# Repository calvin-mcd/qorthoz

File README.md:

# qorthoz

qorthoz is an ortholinear 10.25u qaz compatible pcb with usb c and jst ports for case compatibility, rgb breakout strip and 6 additional pins for switch or rotary extensions.

## Layout

## Pictures

## Firmware

Firmware is written for vial and the source code is provided for edits.

## RGB Strip

Please note that the PCB is using a STM32 MCU which runs on 3v3 logic. Using a 5V rgb strip can sometimes interfere with the 3v3 Data Signal from the MCU. If you use a 5V rgb strip solder Data IN and GND to the beginning of the strip but *DO NOT* solder power to the beginning but anywhere else on the strip. This should be enough to avoid 5V Power interference with the 3v3 Data IN.

## Disclaimer

This PCB has been fully tested and is confirmed to work. However, no-one involved in this project is responsible for any usage issues that may arise. Order at your own risk. Feel free to edit, modify and otherwise utilise these files.

## License

This project is released under the GPL v3 License. Please refer to the LICENCE file.

## Credits

This pcb has been made on request kriscovery. Do check out their beautiful qaz and qez compatible cases! https://www.printables.com/@kriscovery

The silkscreen logo has been taken from the german 40s keyboard discord ClackTales!

As always big thanks to the many people who helped me and inspired this board!

Any questions, contact Calvin0563 on Discord.

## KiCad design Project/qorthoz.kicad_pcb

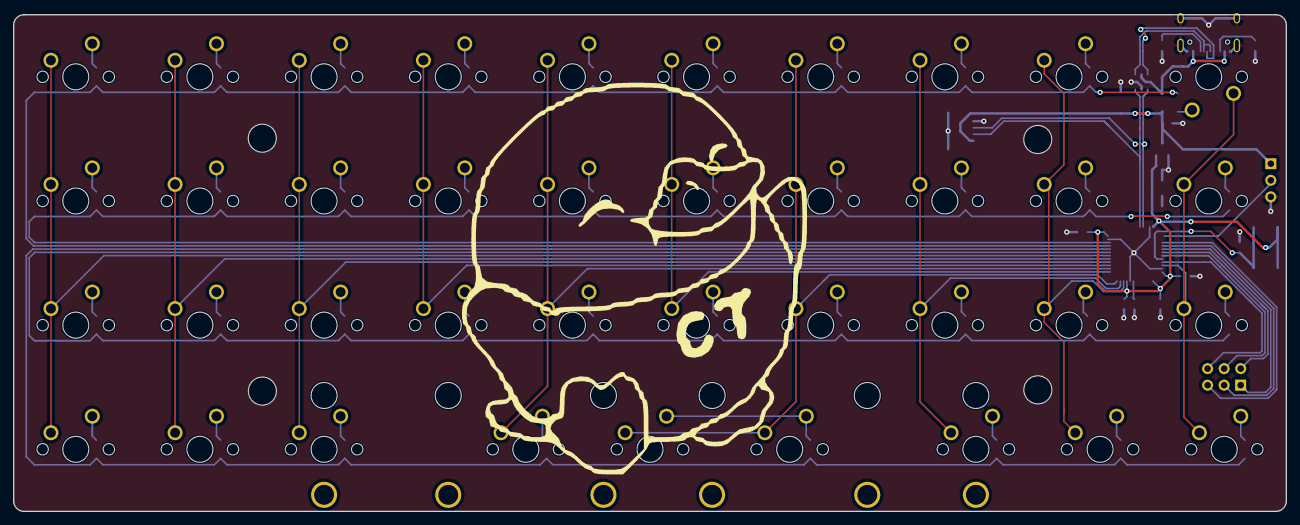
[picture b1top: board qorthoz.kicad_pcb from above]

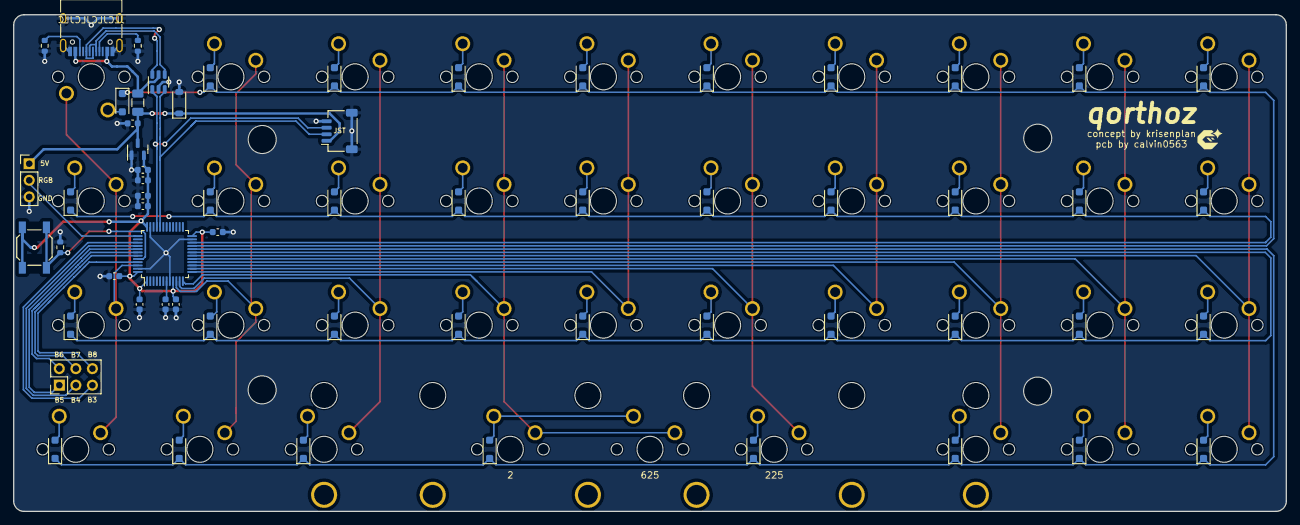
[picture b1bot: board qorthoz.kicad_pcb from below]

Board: 2 copper layers, 195.3 x 76.2 mm, 103 parts (61 on the bottom side), 71 nets.

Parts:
C1, C2, C4: 1uF; C_0603_1608Metric
C3: 4.7uF; C_0603_1608Metric
C5, C6, C7, C8, C9, C10: 100nF; C_0603_1608Metric
D1, D2, D3, D4, D5, D6, D7, D8, D9, D10, D11, D12, D13, D14, D15, D16, D17, D18, D19, D20, D21, D22, D23, D24, D25, D26, D27, D28, D29, D30, D31, D32, D33, D34, D35, D36, D37, D38: D_Small; D_SOD-123F
D_PWR1: SMF9.0CA; D_SOD-123
F1: 500mA; Fuse_1206_3216Metric
J1: USB_C_Receptacle_USB2.0; USB_C_Receptacle_HRO_TYPE-C-31-M-12
J2: Conn_01x03_Socket; PinHeader_1x03_P2.54mm_Vertical
J3: JST SH; JST_SH_SM04B-SRSS-TB_1x04-1MP_P1.00mm_Horizontal
J4: Conn_01x06; PinHeader_2x03_P2.54mm_Vertical
MX1, MX2, MX3, MX4, MX5, MX6, MX7, MX8, MX9, MX11, MX12, MX13, MX14, MX15, MX16, MX17, MX18, MX19, MX21, MX22, MX23, MX24, MX25, MX26, MX27, MX28, MX29, MX31, MX32, MX33, MX34, MX35, MX36, MX37, MX38, MX39: MX_SW_solder; SW_MX_1u
MX10, MX20, MX30: MX_SW_solder; SW_MX_1.25u
R1, R2: 5k1; R_0603_1608Metric
R3: 10k; R_0603_1608Metric
S1: MX_stab; STAB_MX_P_2.25u
S2: MX_stab; STAB_MX_P_2u
S3: MX_stab; STAB_MX_P_6.25u
SW1: SKQGABE010; SW_SPST_SKQG_WithoutStem
U1: USBLC6-2SC6; SOT-23-6
U2: STM32F072C8Tx; LQFP-48_7x7mm_P0.5mm
U3: XC6206PxxxMR-Regulator_Linear; SOT-23

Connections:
+3V3: C2.2, C3.1, C4.1, C5.1, C6.1, C7.1, C8.1, C9.1, SW1.1, U2.1 (VBAT), U2.9 (VDDA), U2.24 (VDD), U2.36 (VDDIO2), U2.48 (VDD), U3.2 (VO)
+5V: C1.2, D_PWR1.1 (A1), F1.2, J2.1, J3.1, U3.3 (VI)
/CC1: J1.A5 (CC1), R1.1
/CC2: J1.B5 (CC2), R2.1
B3: J4.5, U2.39 (PB3)
B4: J4.3, U2.40 (PB4)
B5: J4.1, U2.41 (PB5)
B6: J4.2, U2.42 (PB6)
B7: J4.4, U2.43 (PB7)
B8: J4.6, U2.45 (PB8)
BOOT0: R3.1, SW1.2, U2.44 (BOOT0)
COL0: MX1.1, MX11.1, MX21.1, MX31.1, U2.18 (PB0)
COL1: MX2.1, MX12.1, MX22.1, MX32.1, U2.17 (PA7)
COL2: MX3.1, MX13.1, MX23.1, MX33.1, U2.16 (PA6)
COL3: MX4.1, MX14.1, MX24.1, U2.15 (PA5)
COL4: MX5.1, MX15.1, MX25.1, MX34.1, U2.14 (PA4)
COL5: MX6.1, MX16.1, MX26.1, U2.13 (PA3)
COL6: MX7.1, MX17.1, MX27.1, MX35.1, MX39.1, U2.12 (PA2)
COL7: MX8.1, MX18.1, MX28.1, MX36.1, U2.11 (PA1)
COL8: MX9.1, MX19.1, MX29.1, MX37.1, U2.10 (PA0)
COL9: MX10.1, MX20.1, MX30.1, MX38.1, U2.46 (PB9)
D_N: J3.2, U1.3 (I/O2), U2.32 (PA11)
D_P: J3.3, U1.1 (I/O1), U2.33 (PA12)
D_USB_N: J1.A7 (D-), J1.B7 (D-), U1.4 (I/O2)
D_USB_P: J1.A6 (D+), J1.B6 (D+), U1.6 (I/O1)
GND: C1.1, C2.1, C3.2, C4.2, C5.2, C6.2, C7.2, C8.2, C9.2, C10.2, D_PWR1.2 (A2), J1.A1 (GND), J1.A12 (GND), J1.B1 (GND), J1.B12 (GND), J1.S1 (SHIELD), J2.3, J3.4, J3.MP (MountPin), R1.2, R2.2, R3.2, U1.2 (GND), U2.8 (VSSA), U2.23 (VSS), U2.35 (VSS), U2.47 (VSS), U3.1 (GND)
NRST: C10.1, U2.7 (NRST)
unnamed: D1.2 (A), MX1.2
unnamed: D2.2 (A), MX2.2
unnamed: D3.2 (A), MX3.2
unnamed: D4.2 (A), MX4.2
unnamed: D5.2 (A), MX5.2
unnamed: D6.2 (A), MX6.2
unnamed: D7.2 (A), MX7.2
unnamed: D8.2 (A), MX8.2
unnamed: D9.2 (A), MX9.2
unnamed: D10.2 (A), MX10.2
unnamed: D11.2 (A), MX11.2
unnamed: D12.2 (A), MX12.2
unnamed: D13.2 (A), MX13.2
unnamed: D14.2 (A), MX14.2
unnamed: D15.2 (A), MX15.2
unnamed: D16.2 (A), MX16.2
unnamed: D17.2 (A), MX17.2
unnamed: D18.2 (A), MX18.2
unnamed: D19.2 (A), MX19.2
unnamed: D20.2 (A), MX20.2
unnamed: D21.2 (A), MX21.2
unnamed: D22.2 (A), MX22.2
unnamed: D23.2 (A), MX23.2
unnamed: D24.2 (A), MX24.2
unnamed: D25.2 (A), MX25.2
unnamed: D26.2 (A), MX26.2
unnamed: D27.2 (A), MX27.2
unnamed: D28.2 (A), MX28.2
unnamed: D29.2 (A), MX29.2
unnamed: D30.2 (A), MX30.2
unnamed: D31.2 (A), MX31.2
unnamed: D32.2 (A), MX32.2
unnamed: D33.2 (A), MX33.2
unnamed: D34.2 (A), MX34.2
unnamed: D35.2 (A), MX35.2, MX39.2
unnamed: D36.2 (A), MX36.2
unnamed: D37.2 (A), MX37.2
unnamed: D38.2 (A), MX38.2
RGB: J2.2, U2.37 (PA14)
ROW0: D1.1 (K), D2.1 (K), D3.1 (K), D4.1 (K), D5.1 (K), D6.1 (K), D7.1 (K), D8.1 (K), D9.1 (K), D10.1 (K), U2.21 (PB10)
ROW1: D11.1 (K), D12.1 (K), D13.1 (K), D14.1 (K), D15.1 (K), D16.1 (K), D17.1 (K), D18.1 (K), D19.1 (K), D20.1 (K), U2.22 (PB11)
ROW2: D21.1 (K), D22.1 (K), D23.1 (K), D24.1 (K), D25.1 (K), D26.1 (K), D27.1 (K), D28.1 (K), D29.1 (K), D30.1 (K), U2.19 (PB1)
ROW3: D31.1 (K), D32.1 (K), D33.1 (K), D34.1 (K), D35.1 (K), D36.1 (K), D37.1 (K), D38.1 (K), U2.20 (PB2)
VBUS: F1.1, J1.A4 (VBUS), J1.A9 (VBUS), J1.B4 (VBUS), J1.B9 (VBUS), U1.5 (VBUS)

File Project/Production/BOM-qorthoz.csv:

Comment,Designator,Footprint,LCSC
SKQGABE010,SW1,SW_SPST_SKQG_WithoutStem,C115351
1uF,"C1,C2,C4",C_0603_1608Metric,C15849
JST SH,J3,JST_SH_SM04B-SRSS-TB_1x04-1MP_P1.00mm_Horizontal,C160404
USB_C_Receptacle_USB2.0,J1,USB_C_Receptacle_HRO_TYPE-C-31-M-12,C165948
4.7uF,C3,C_0603_1608Metric,C19666
10k,R3,R_0603_1608Metric,C2139679
5k1,"R1,R2",R_0603_1608Metric,C14677
USBLC6-2SC6,U1,SOT-23-6,C2827654
100nF,"C10,C5,C6,C7,C8,C9",C_0603_1608Metric,C14663
XC6206PxxxMR-Regulator_Linear,U3,SOT-23,C5446
D_Small,"D1,D10,D11,D12,D13,D14,D15,D16,D17,D18,D19,D2,D20,D21,D22,D23,D24,D25,D26,D27,D28,D29,D3,D30,D31,D32,D33,D34,D35,D36,D37,D38,D4,D5,D6,D7,D8,D9",D_SOD-123F,C64898
500mA,F1,Fuse_1206_3216Metric,C70076
SMF9.0CA,D_PWR1,D_SOD-123,C707469
STM32F072C8Tx,U2,LQFP-48_7x7mm_P0.5mm,C81720

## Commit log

2023-10-22 project organised and cleaned up
2023-10-23 readme update
2024-01-13 backup
2024-11-26 backuo
